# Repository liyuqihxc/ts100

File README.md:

# ts100
A custom ts100 soldering iron

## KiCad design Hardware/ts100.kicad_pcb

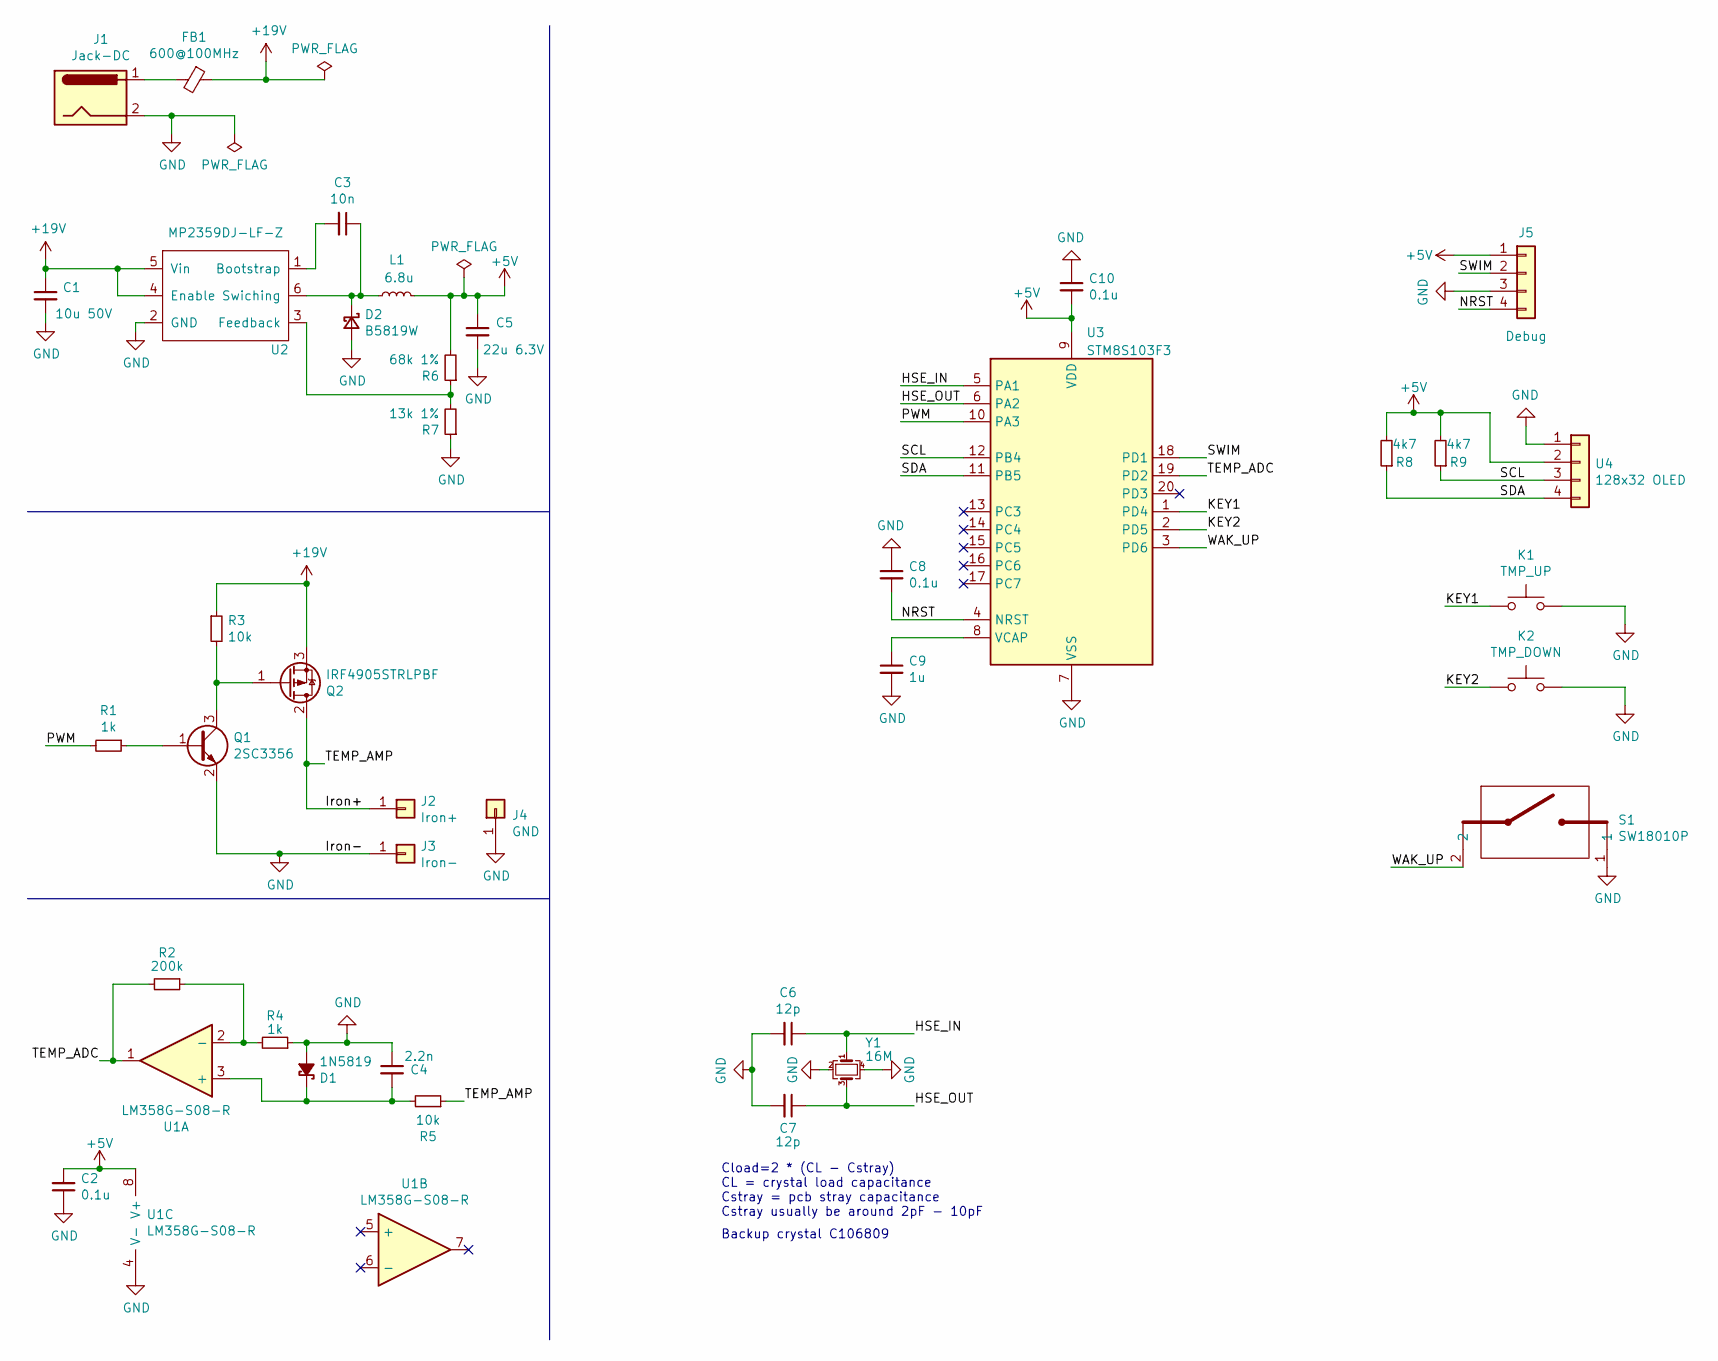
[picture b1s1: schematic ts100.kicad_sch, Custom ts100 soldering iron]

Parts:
C1: 10u 50V; C_1210_3225Metric; PartNum C15850
C2, C8: 0.1u; C_0402_1005Metric
C3: 10n; C_0603_1608Metric
C4: 2.2n; C_0402_1005Metric
C5: 22u 6.3V; C_0603_1608Metric; PartNum C86295
C6, C7: 12p; C_0402_1005Metric
C9: 1u; C_0603_1608Metric; PartNum C107372
C10: 0.1u; C_0603_1608Metric
D1: 1N5819; D_SOD-123; PartNum C437199
D2: B5819W; D_SOD-123
FB1: 600@100MHz; L_0805_2012Metric; PartNum C21286
J1: Jack-DC; BarrelJack_CLIFF_FC681465S_SMT_Horizontal; PartNum C720583
J2: Iron+; Fuseholder_5x20mm_inline; PartNum C3130
J3: Iron-; Fuseholder_5x20mm_inline; PartNum C3130
J4: GND; Fuseholder_5x20mm_inline; PartNum C3130
J5: Debug; PinHeader_1x04_P1.27mm_Vertical; PartNum C3408
K1: TMP_UP; SMD,4.6x1.82x3.5mm; PartNum C319392
K2: TMP_DOWN; SMD,4.6x1.82x3.5mm; PartNum C319392
L1: 6.8u; L_1008_2520Metric; PartNum C576569
Q1: 2SC3356; SOT-23; PartNum C193010
Q2: IRF4905STRLPBF; TO-263-2; PartNum C2620
R1, R4: 1k; R_0402_1005Metric
R2: 200k; R_0402_1005Metric
R3, R5: 10k; R_0402_1005Metric
R6: 68k 1%; R_0402_1005Metric
R7: 13k 1%; R_0402_1005Metric
R8, R9: 4k7; R_0402_1005Metric
S1: SW18010P; C_Radial_D5.0mm_H5.0mm_P2.00mm; PartNum C2681585
U1: LM358G-S08-R; SOP-8_3.9x4.9mm_P1.27mm; PartNum C71101
U2: MP2359DJ-LF-Z; SOT-23-6; PartNum C89300
U3: STM8S103F3; TSSOP-20_4.4x6.5mm_P0.65mm
U4: 128x32 OLED; PinSocket_1x04_P2.54mm_Vertical; PartNum *
Y1: 16M; Crystal_SMD_3225-4Pin_3.2x2.5mm

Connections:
+5V: C2.2, C5.1, C10.2, J5.1, L1.2, R6.2, R8.2, R9.2, U1.8 (V+), U3.9 (VDD), U4.2
+15V: C1.1, FB1.1, Q2.3 (S), R3.1, U2.4 (Enable), U2.5 (Vin)
/HSE_IN: C6.1, U3.5 (PA1), Y1.1
/HSE_OUT: C7.1, U3.6 (PA2), Y1.3
/Iron+: J2.1, Q2.2 (D), R5.1
/KEY1: K1.1, U3.1 (PD4)
/KEY2: K2.1, U3.2 (PD5)
/NRST: C8.2, J5.4, U3.4 (NRST)
/PWM: R1.2, U3.10 (PA3)
/SCL: R9.1, U3.12 (PB4), U4.3
/SDA: R8.1, U3.11 (PB5), U4.4
/SWIM: J5.2, U3.18 (PD1)
/TEMP_ADC: R2.2, U1.1, U3.19 (PD2)
/WAK_UP: S1.2, U3.3 (PD6)
GND: C1.2, C2.1, C4.1, C5.2, C6.2, C7.2, C8.1, C9.2, C10.1, D1.2 (A), D2.2 (A), J1.2, J3.1, J4.1, J5.3, K1.2, K2.2, Q1.2 (E), R4.1, R7.1, S1.1, U1.4 (V-), U2.2 (GND), U3.7 (VSS), U4.1, Y1.2, Y1.4
unnamed: C3.1, D2.1 (K), L1.1, U2.6 (Swiching)
unnamed: C3.2, U2.1 (Bootstrap)
unnamed: C4.2, D1.1 (K), R5.2, U1.3 (+)
unnamed: C9.1, U3.8 (VCAP)
unnamed: FB1.2, J1.1
unnamed: Q1.1 (B), R1.1
unnamed: Q1.3 (C), Q2.1 (G), R3.2
unnamed: R2.1, R4.2, U1.2 (-)
unnamed: R6.1, R7.2, U2.3 (Feedback)

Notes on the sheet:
Cload=2 * (CL - Cstray) CL = crystal load capacitance Cstray = pcb stray capacitance Cstray usually be around 2pF - 10pF
Backup crystal C106809

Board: 2 copper layers, 38 parts (5 on the bottom side), 24 nets, no tracks yet.

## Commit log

2021-09-15 init
2021-09-15 hardware
2021-09-16 parts
2021-09-17 remove old cmake config
2021-09-17 cmake
2021-09-18 update gitmodules
2021-09-27 cpp intelli sense
2021-09-27 firmware
2021-12-29 修改原理图
2021-12-30 重绘电源
2021-12-31 修改封装
2022-11-18 重绘PCB
2022-11-23 核对封装
